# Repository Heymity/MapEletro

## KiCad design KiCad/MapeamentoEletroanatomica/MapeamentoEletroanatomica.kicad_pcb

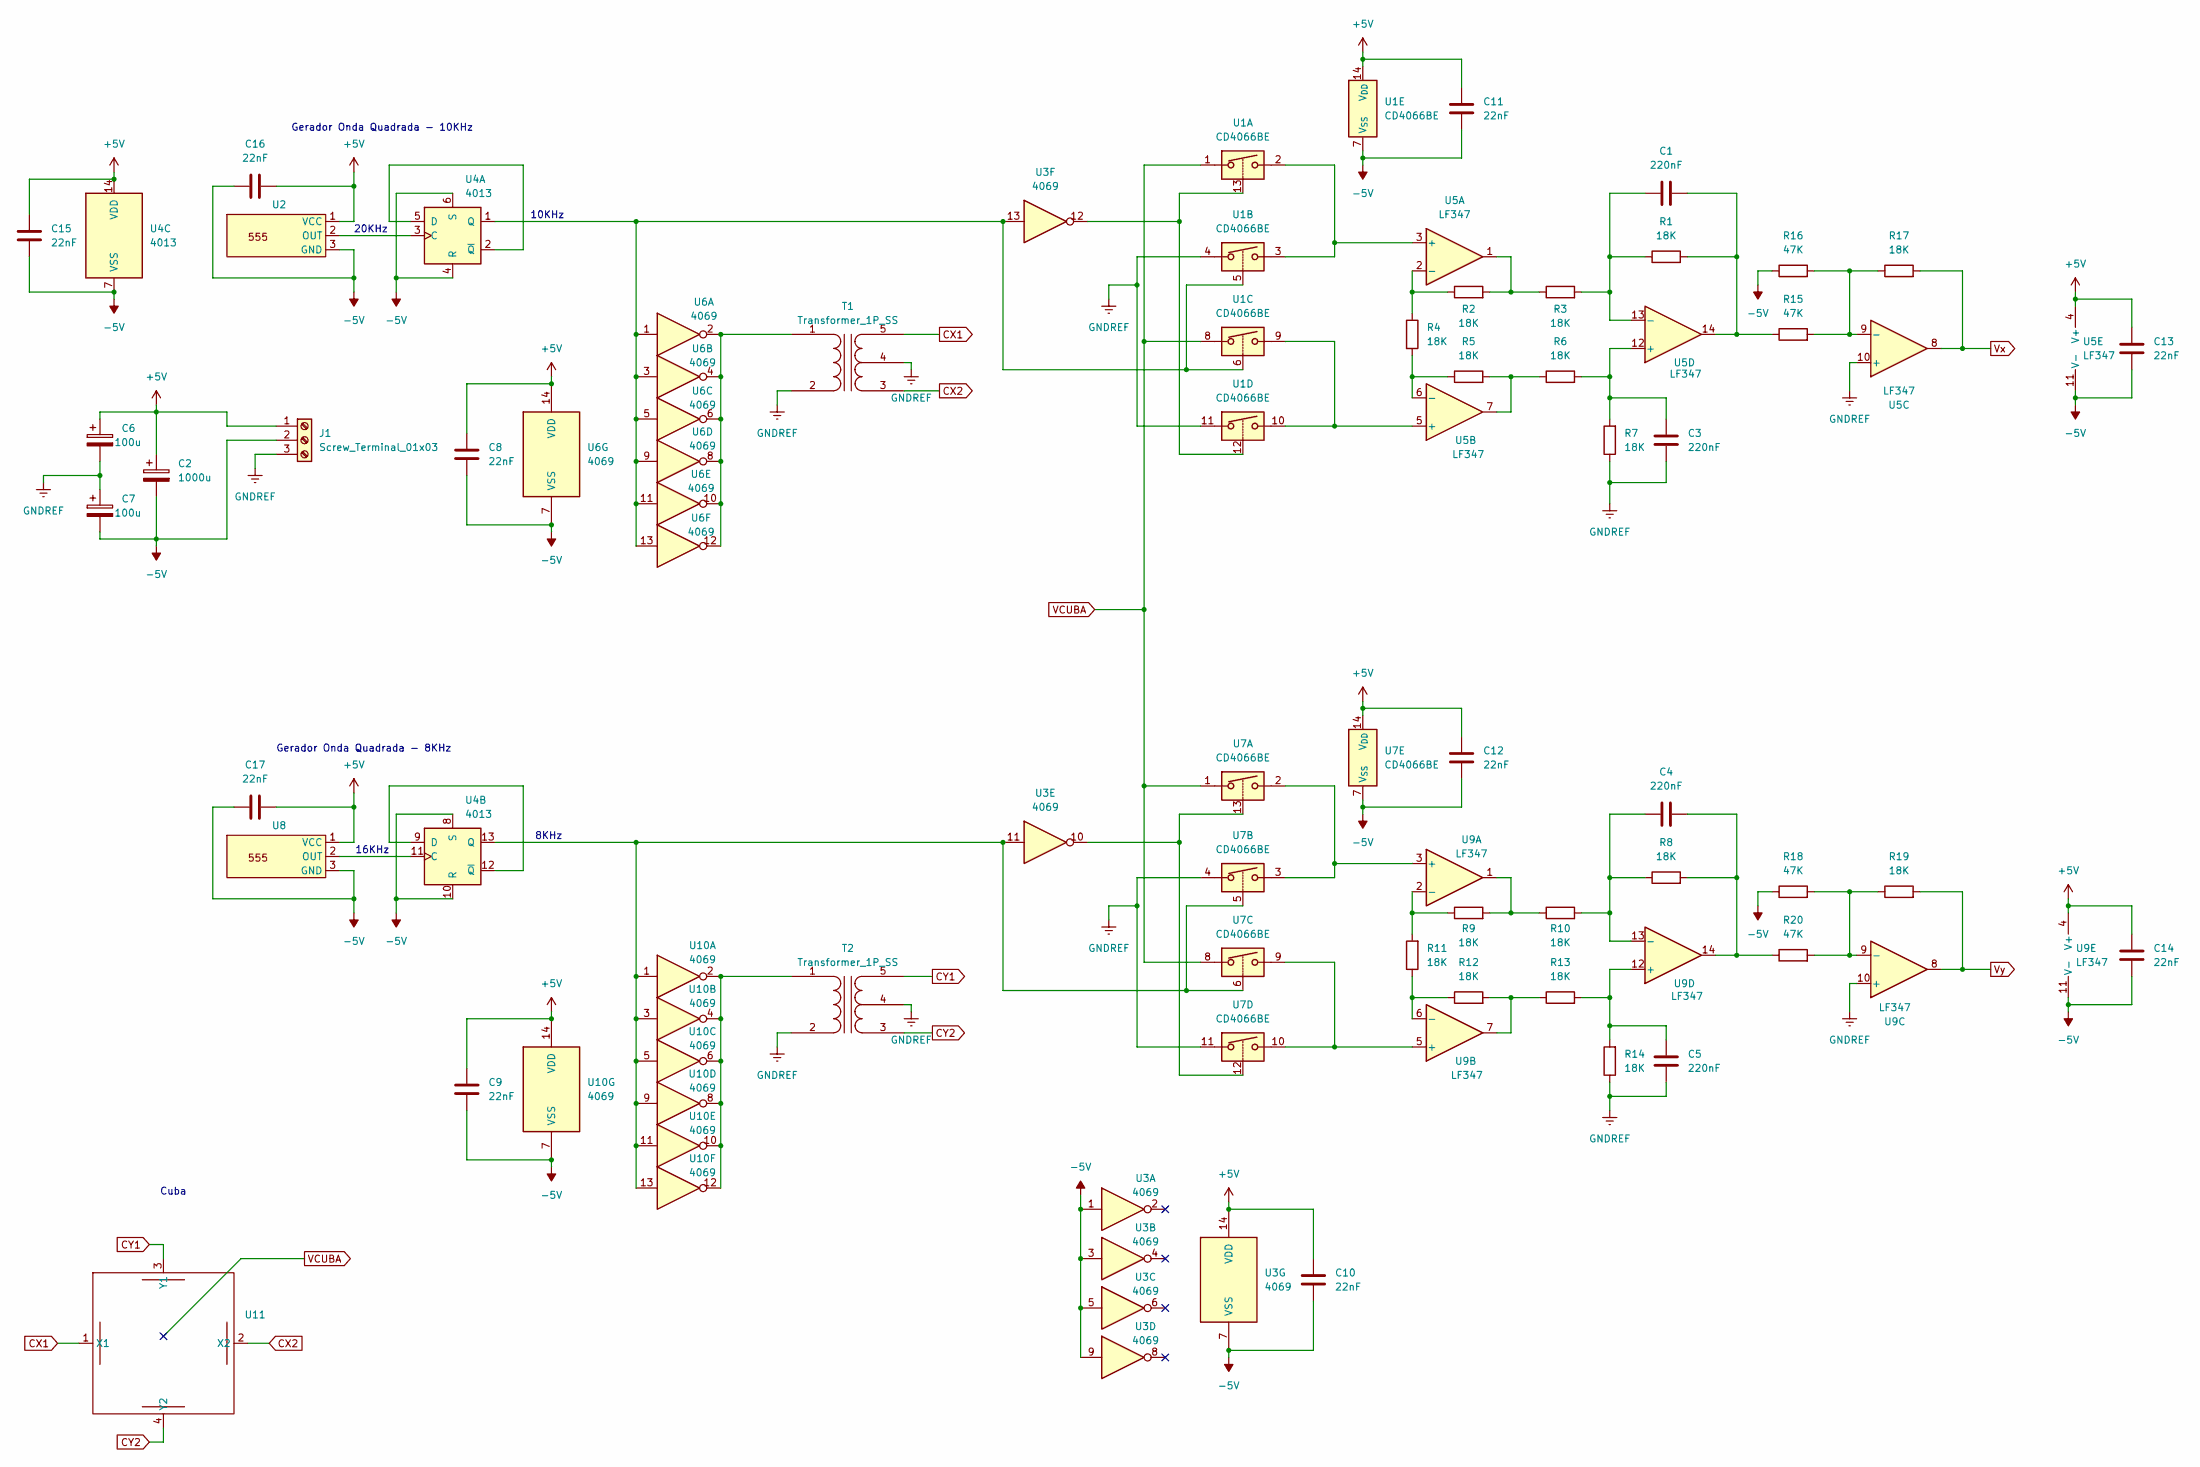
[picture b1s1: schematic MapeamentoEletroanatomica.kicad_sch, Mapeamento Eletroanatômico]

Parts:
C1, C3, C4, C5: 220nF; C_Radial_D4.0mm_H5.0mm_P1.50mm
C2: 1000u; CP_Radial_D8.0mm_P5.00mm
C6, C7: 100u; CP_Radial_D8.0mm_P5.00mm
C8, C9, C10, C11, C12, C13, C14, C15, C16, C17: 22nF; C_Radial_D4.0mm_H5.0mm_P1.50mm
J1: Screw_Terminal_01x03; TerminalBlock_Altech_AK300-3_P5.00mm
R1, R2, R3, R4, R5, R6, R7, R8, R9, R10, R11, R12, R13, R14, R17, R19: 18K; R_Axial_DIN0207_L6.3mm_D2.5mm_P10.16mm_Horizontal
R15, R16, R18, R20: 47K; R_Axial_DIN0207_L6.3mm_D2.5mm_P10.16mm_Horizontal
T1, T2: Transformer_1P_SS; PinHeader_1x05_P2.54mm_Vertical
U1, U7: CD4066BE; DIP-14_W7.62mm_Socket
U2, U8: PinHeader_1x03_P2.54mm_Vertical
U3, U6, U10: 4069; DIP-14_W7.62mm_Socket
U4: 4013; DIP-14_W7.62mm_Socket
U5, U9: LF347; DIP-14_W7.62mm_Socket
U11: PinHeader_1x04_P2.54mm_Vertical

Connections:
+5V: C2.1, C6.1, C8.2, C9.2, C10.2, C11.2, C12.2, C13.2, C14.2, C15.2, C16.1, C17.1, J1.1, U1.14 (V_{DD}), U2.1 (VCC), U3.14 (VDD), U4.14 (VDD), U5.4 (V+), U6.14 (VDD), U7.14 (V_{DD}), U8.1 (VCC), U9.4 (V+), U10.14 (VDD)
-5V: C2.2, C7.2, C8.1, C9.1, C10.1, C11.1, C12.1, C13.1, C14.1, C15.1, C16.2, C17.2, J1.2, R16.1, R18.1, U1.7 (V_{SS}), U2.3 (GND), U3.1, U3.3, U3.5, U3.7 (VSS), U3.9, U4.4 (R), U4.6 (S), U4.7 (VSS), U4.8 (S), U4.10 (R), U5.11 (V-), U6.7 (VSS), U7.7 (V_{SS}), U8.3 (GND), U9.11 (V-), U10.7 (VSS)
CX1: T1.5 (SB), U11.1 (X1)
CX2: T1.3 (SA), U11.2 (X2)
CY1: T2.5 (SB), U11.3 (Y1)
CY2: T2.3 (SA), U11.4 (Y2)
GNDREF: C3.1, C5.1, C6.2, C7.1, J1.3, R7.1, R14.1, T1.2 (AB), T1.4 (SC), T2.2 (AB), T2.4 (SC), U1.4, U1.11, U5.10 (+), U7.4, U7.11, U9.10 (+)
unnamed: C1.2, R1.2, R15.1, U5.14
unnamed: C4.2, R8.2, R20.1, U9.14
unnamed: R2.2, R3.1, U5.1
unnamed: R5.2, R6.1, U5.7
unnamed: R9.2, R10.1, U9.1
unnamed: R12.2, R13.1, U9.7
unnamed: T1.1 (AA), U6.2, U6.4, U6.6, U6.8, U6.10, U6.12
unnamed: T2.1 (AA), U10.2, U10.4, U10.6, U10.8, U10.10, U10.12
unnamed: U1.12, U1.13, U3.12
unnamed: U2.2 (OUT), U4.3 (C)
unnamed: U3.10, U7.12, U7.13
unnamed: U4.2 (~Q), U4.5 (D)
unnamed: U1.5, U1.6, U3.13, U4.1 (Q), U6.1, U6.3, U6.5, U6.9, U6.11, U6.13
unnamed: U4.11 (C), U8.2 (OUT)
unnamed: U4.9 (D), U4.12 (~Q)
unnamed: U3.11, U4.13 (Q), U7.5, U7.6, U10.1, U10.3, U10.5, U10.9, U10.11, U10.13
unnamed: U1.2, U1.3, U5.3 (+)
unnamed: R2.1, R4.1, U5.2 (-)
unnamed: U1.9, U1.10, U5.5 (+)
unnamed: R4.2, R5.1, U5.6 (-)
unnamed: R15.2, R16.2, R17.1, U5.9 (-)
unnamed: C3.2, R6.2, R7.2, U5.12 (+)
unnamed: C1.1, R1.1, R3.2, U5.13 (-)
unnamed: U7.2, U7.3, U9.3 (+)
unnamed: R9.1, R11.2, U9.2 (-)
unnamed: U7.9, U7.10, U9.5 (+)
unnamed: R11.1, R12.1, U9.6 (-)
unnamed: R18.2, R19.1, R20.2, U9.9 (-)
unnamed: C5.2, R13.2, R14.2, U9.12 (+)
unnamed: C4.1, R8.1, R10.2, U9.13 (-)
VCUBA: U1.1, U1.8, U7.1, U7.8; also elsewhere on the board
Vx: R17.2, U5.8
Vy: R19.2, U9.8

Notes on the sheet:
Gerador Onda Quadrada - 8KHz
Gerador Onda Quadrada - 10KHz
Cuba
10KHz
8KHz
20KHz
16KHz

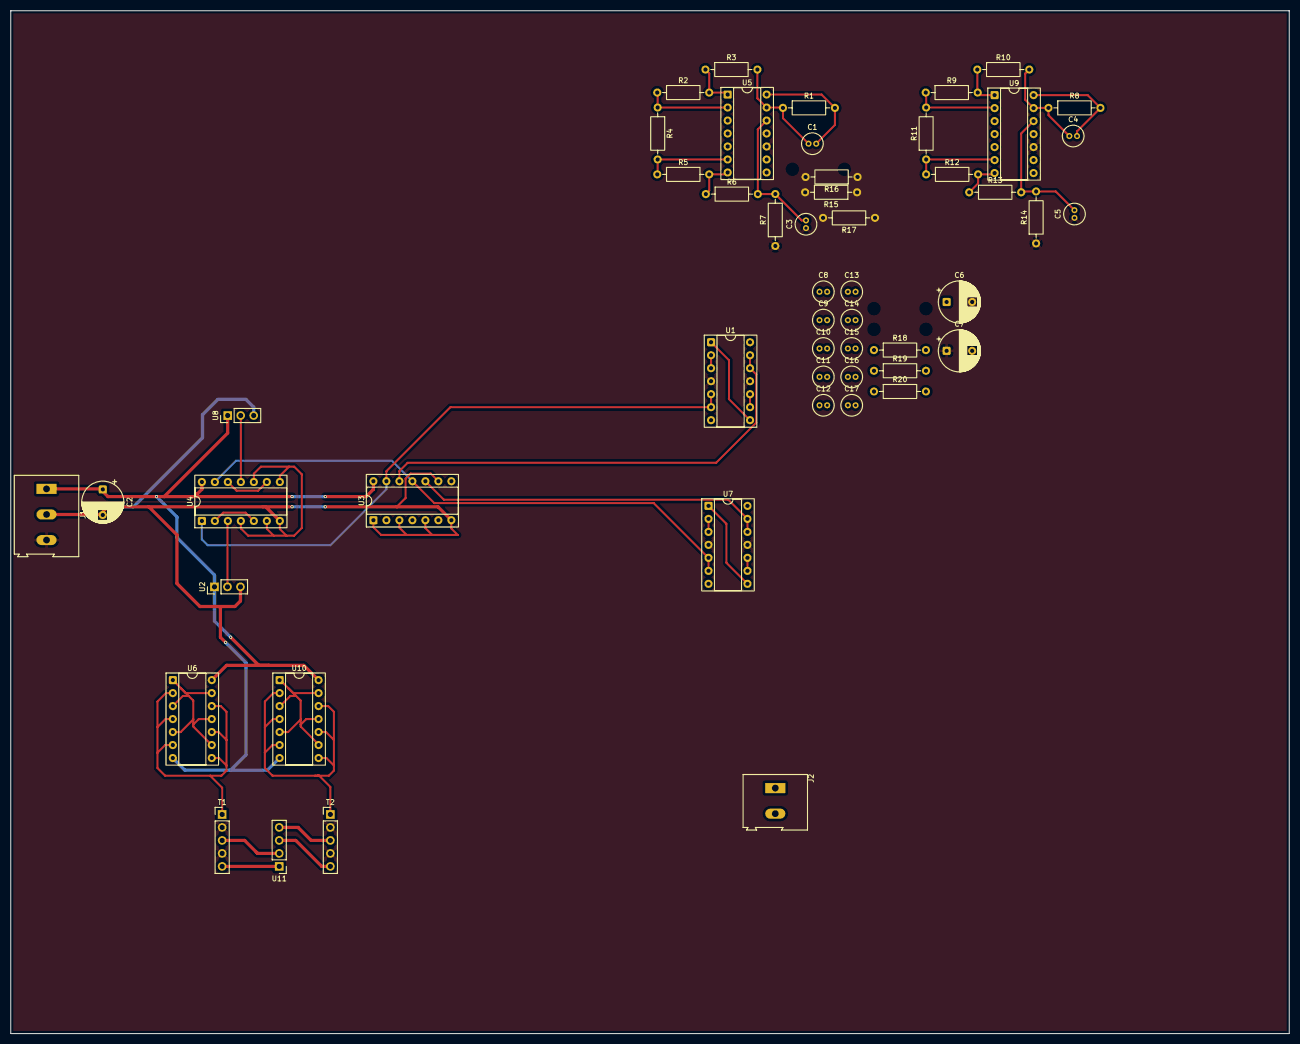
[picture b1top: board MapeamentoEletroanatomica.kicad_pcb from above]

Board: 2 copper layers, 250.0 x 200.0 mm, 52 parts (0 on the bottom side), 40 nets.

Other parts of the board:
J2: Screw_Terminal_01x01; TerminalBlock_Altech_AK300-2_P5.00mm

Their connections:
VCUBA: J2.1; also elsewhere on the board

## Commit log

2025-08-16 Upload Files
2025-08-16 [ImgBot] Optimize images
    *Total -- 1,114.58kb -> 958.49kb (14%)
    /1x/MontagemCuba.png -- 8.27kb -> 4.14kb (49.94%)
    /1x/MontagemCircuito.png -- 11.95kb -> 7.42kb (37.93%)
    /AmpOp/RespostaEmFrequenciaAmpOp.png -- 172.25kb -> 133.70kb (22.38%)
    /Cuba/RespostaEmFrequencia.png -- 171.50kb -> 142.88kb (16.69%)
    /DeadBug.png -- 599.26kb -> 532.70kb (11.11%)
